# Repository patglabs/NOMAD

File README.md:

# NOMAD 
A laptop designed to be customisable, portable and open source

if you're in the hc slack make sure to join #pats-basement

## STATUS : ON HOLD DUE TO LACK OF FUNDS

## In brief:
Nomad is a laptop ive designed and am designing that features a lattepanda mu n100 at its center which handles all the compute. It uses a custom mainboard pcb that I designed to have 2 usb 3 type A ports exposed to the outside,
1 usb c 2.0 and 1 internal usb 2.0 which will go into an internal usb hub so that i can put an rtl sdr inside the laptop so i have an sdr everywhere i go. It uses a 14 inch hd display. A thinkpad keyboard. 3-4 5000mah lithium ion batteries in the standard
7mm thickness. Its passively cooled using an anodized aluminum sheet that will cover most of the bottom with the rest being 3d printed ideally in petg and assuming all goes to plan around it will be around 1.7cm thick. I estimate that it can acheive at least 6 hours of battery life with 4 5000mah battery while doing lite tasks. It also has m.2 slots. M key for nvme and e key for a wireless adapter.

## The vision:

A while ago i remember seeing a youtube short that really stuck with me, it was about a "hacker laptop and the short explained how it used a raspberry pi inside and had 18650 batteries and all and while it was a cool project i was blown away by the price, it costed over 1k usd and it was not very powerfull nor portable it felt like more of a cool gimmick than a tool. So I said one day I want to make something like that but ill make it the way i want. Itl have the things i want in a laptop: being compact and sturdy, easily fixable if something breaks, cheap, i can put custom stuff in it (like an rtl-sdr) and i wanted it to have decent battery life so that i can bring it anywhere and if i'm stuck somewhere with no power for 3 hours i can still work on stuff on it. Basically something that can be daily drivable when I dont have access to my desktop.

### pcb

Its pretty crowded, I recomend you open up the pcb in kicad you'll be able to zoom into stuff

(missing the 2 usb3 ports and the ddr4 so-dimm connector

note: pcb V2 is the latest pcb, but production wise they are the same its just a redraw of the schematic
so you want to look at the v2

### cad

### Bom

| Item | Price | Link |
|------|-------|------|
| Lattepanda MU + Lite Dev Carrier Board | 180 USD | [DFRobot](https://www.dfrobot.com/kit-004.html) |
| Display Controller | 22 USD | [AliExpress](https://www.aliexpress.com/item/1005008432586523.html?spm=a2g0o.productlist.main.12.6c4bwR7lwR7l8y&algo_pvid=8593971f-0f25-4dac-ac2b-4313578de187&algo_exp_id=8593971f-0f25-4dac-ac2b-4313578de187-11&pdp_ext_f=%7B%22order%22%3A%22-1%22%2C%22eval%22%3A%221%22%7D&pdp_npi=4%40dis%21CAD%2131.75%2126.99%21%21%21162.57%21138.20%21%402103247417527988213296838e3ecd%2112000045073927194%21sea%21CA%216086132031%21X&curPageLogUid=1h1893jWQeCE&utparam-url=scene%3Asearch%7Cquery_from%3A) |
| Display 14 inch | 42 USD | [AliExpress](https://www.aliexpress.com/item/1005003386237483.html?spm=a2g0o.productlist.main.20.787a5f1dEl49la&algo_pvid=1de636ed-d35d-4aee-a0d8-9a6b0865f511&algo_exp_id=1de636ed-d35d-4aee-a0d8-9a6b0865f511-19&pdp_ext_f=%7B%22order%22%3A%2223%22%2C%22eval%22%3A%221%22%7D&pdp_npi=4%40dis%21CAD%2168.99%2168.99%21%21%2149.21%2149.21%21%40210318ec17527987558765212ed2de%2112000025538273862%21sea%21CA%216086132031%21X&curPageLogUid=DP21csvKEzq9&utparam-url=scene%3Asearch%7Cquery_from%3A) |
| Reinforcement Sheet for Display | 4.50 USD | [AliExpress](https://www.aliexpress.com/item/1005005966208898.html?spm=a2g0o.productlist.main.4.46b44b90s4itPe&algo_pvid=2cadd10b-1e23-4d8a-baaa-58015ebbfa84&algo_exp_id=2cadd10b-1e23-4d8a-baaa-58015ebbfa84-3&pdp_ext_f=%7B%22order%22%3A%22911%22%2C%22eval%22%3A%221%22%7D&pdp_npi=4%40dis%21CAD%215.69%215.69%21%21%2129.16%2129.16%21%402103244417534139299131566ef5c8%2112000035086418949%21sea%21CA%216086132031%21X&curPageLogUid=P45FPnknGnQg&utparam-url=scene%3Asearch%7Cquery_from%3A) |
| SODIMM DDR4 Connector (C2979963) | - | [JLCPCB](https://jlcpcb.com/partdetail/FOXCONN-ASAA823_EARB07H/C2979963) |
| 5000 mAh Battery | 30 CAD × 3–4 | [Amazon](https://www.amazon.ca/5000mAh-755590-Lithium-Replacement-Electronic/dp/B0BG85CMFL/ref=sr_1_1_sspa?crid=1VN50572QX28K&dib=eyJ2IjoiMSJ9.UH2iT11CrxzaQwfjEOyYPhK1U5jypSDZNWR4AsOAj6AqUhiNM-AfuSVTdCHuEgDrhX1ioglR6OQ_EnFGpm1RMRGhI8XFnnH-OlCwdBPSY1DBLp_jPFmBZIQ1OtFXrNlPgc_Z7XODRqUUBo6_nUXE3vagri2b7yDxdF9CqiwkFz52h7MugKFeGZKHuOtqFd3e4pfhVFPoPNogyl6p7YN8Cja68egJHFHi3pZRJOaOmkVI7mTkMwltDyW_U-2lOJuCL-ofAm3b0rf8hjlGPR3D_fCmjXyqCv1V4x5C1jTn2eI.CyqpkaqJzNKz6gdU7nku_drLzpFhmbIbea_bnupkH2w&dib_tag=se&keywords=lithium+battery+5000mah&qid=1753592235&sprefix=lithium+battery+5000mah%2Caps%2C94&sr=8-1-spons&sp_csd=d2lkZ2V0TmFtZT1zcF9hdGY&psc=1) |
| Mainboard PCB | ~90 USD (estimate) | x |
| ThinkPad Keyboard | ~30–40 USD | - |

Note that I already have the thinkpad keyboard and the 3d printing filament but its pla so ill have to test petg in the future.

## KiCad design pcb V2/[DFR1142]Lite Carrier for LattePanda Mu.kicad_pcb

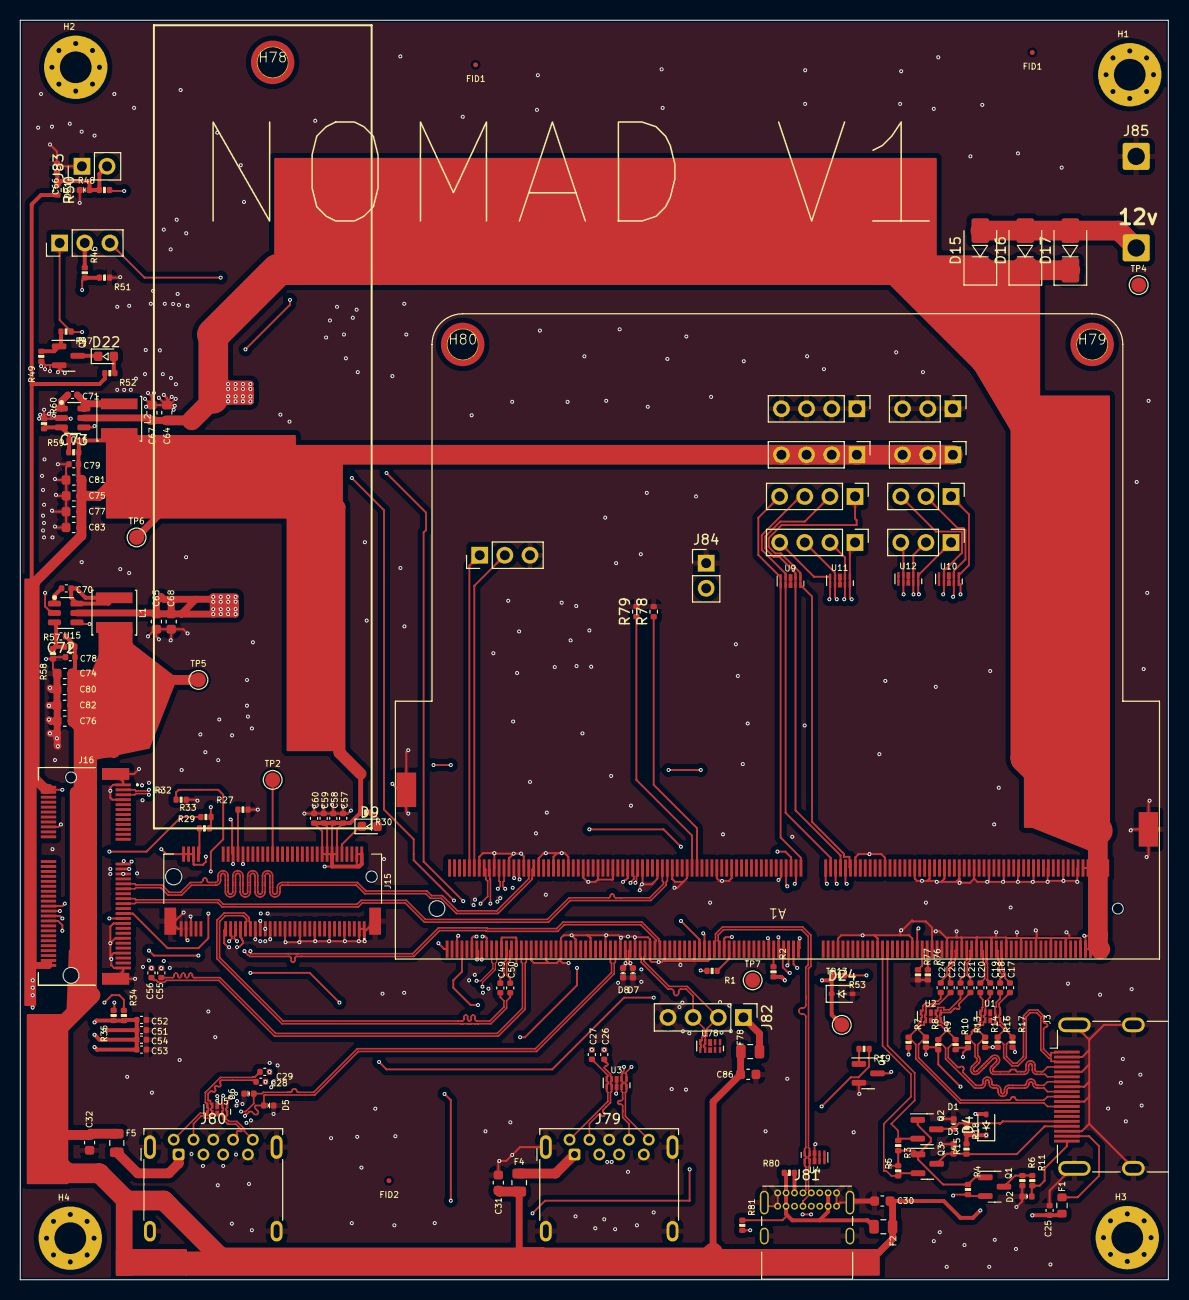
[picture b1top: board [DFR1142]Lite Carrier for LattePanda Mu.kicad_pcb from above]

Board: 4 copper layers, 116.0 x 127.2 mm, 168 parts (0 on the bottom side), 130 nets.

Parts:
A1: LattePanda_Mu; LattePanda_Module_H8.0mm_Horizontal
C17, C18, C19, C20, C21, C22, C23, C24, C25, C26, C27, C28, C29, C52, C54, C58, C60, C70, C71, C78, C79: 100nF/50V; C_0402_1005Metric
C30, C31, C32, C64, C65, C67, C68, C74, C75, C76, C77, C80, C81, C82, C83, C86: 22uF/10V; C_0603_1608Metric
C49, C50, C55, C56: 220nF/50V; C_0402_1005Metric
C51, C53, C57, C59: 10uF/10V; C_0402_1005Metric
C66: 1uF/16V; C_0402_1005Metric
C72, C73: 12pF/50V; C_0402_1005Metric
D1, D2, D3, D5, D6, D7, D8, D21: ESD5V0B03; D_0402_1005Metric
D4: 1N5819WS; D_SOD-323
D9, D22: LED_G; LED_0603_1608Metric
D15, D16, D17: SS54; D_SMA
D24: 3V3 Izt=5mA; D_SOD-323
F1: 6V/50mA; R_0603_1608Metric
F2, F78: 6V/1A; Fuse_0805_2012Metric
F4: 6V/2A; R_0805_2012Metric
F5: 6V/2A; Fuse_0805_2012Metric
FID1, FID1#2, FID2: Fiducial; Fiducial_0.5mm_Mask1mm
H1, H2, H3, H4: MountingHole_Pad; MountingHole_3.2mm_M3_Pad_Via
H78, H79, H80: MountingHole_Pad; MountingHole_3mm_M2_Pad_TopOnly
J1, J8, J10, J11, J14: Conn_01x03_Pin; PinHeader_1x03_P2.54mm_Vertical
J3: HDMI_A; HDMI_A_Molex_208658-1001_Horizontal
J7, J9, J12, J13, J82: Conn_01x04_Pin; PinHeader_1x04_P2.54mm_Vertical
J15: Bus_M.2_Socket_M; PCIe_M.2_Connectors_P=0.5mm_H=4.2mm_KeyM
J16: Bus_M.2_Socket_E; PCIe_M.2_Connectors_P=0.5mm_H=4.2mm_KeyE
J78, J85: Conn_01x01_Pin; SolderWire-1sqmm_1x01_D1.4mm_OD2.7mm
J79, J80: USB3_A; USB3_A_Molex_48393-001
J81: USB_C_Receptacle_USB2.0_16P; USB_C_Receptacle_GCT_USB4085
J83, J84: Conn_01x02_Pin; PinHeader_1x02_P2.54mm_Vertical
JP1: Jumper_3_Bridged12; PinHeader_1x03_P2.54mm_Vertical
L1, L2: 2.2uH/4.3A; L_Sunlord_SWPA4020S
Q1, Q8: 2N7002; SOT-23
Q2, Q3, Q4: 2SK3018; SOT-23
R1, R11, R47: 1K/1%; R_0402_1005Metric
R2, R34, R35, R49, R50, R58, R78, R79: 10K/1%; R_0402_1005Metric
R3, R5, R15, R18, R19, R30, R52, R53: 2.2K/1%; R_0402_1005Metric
R4: 1M/1%; R_0402_1005Metric
R6, R59: 21.5K/1%; R_0402_1005Metric
R7, R8, R9, R10, R13, R14, R16, R17: 470R/1%; R_0402_1005Metric
R27, R29, R32, R33: 0R/1%; R_0402_1005Metric
R46, R48: 100R/1%; R_0402_1005Metric
R51, R76, R77: 100K/1%; R_0402_1005Metric
R57: 75K/1%; R_0402_1005Metric
R60: 4.7K/1%; R_0402_1005Metric
R80, R81: 5.1K/1%; R_0402_1005Metric
TP2, TP4, TP5, TP6, TP7, TP13: TestPoint; TestPoint_Pad_D1.5mm
U1, U2: TPAZ1023-04F; Diodes_UDFN-10_1.0x2.5mm_P0.5mm
U3, U4, U5, U9, U10, U11, U12, U78: ULC0524P; Diodes_UDFN-10_1.0x2.5mm_P0.5mm
U15, U16: SY8253ADC; TSOT-23-6

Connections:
5V_HDMI_VCC: C25.1, D4.1 (K), F1.1, R15.1, R18.1
+3V3: C51.2, C52.2, C53.2, C54.2, C57.2, C58.2, C59.2, C60.2, C73.1, C75.2, C77.2, C79.1, C81.2, C83.2, J13.1, J13.2, J13.3, J13.4, J14.1, J14.2, J14.3, J15.2 (3.3V), J15.4 (3.3V), J15.12 (3.3V), J15.14 (3.3V), J15.16 (3.3V), J15.18 (3.3V), J15.70 (3.3V), J15.72 (3.3V), J15.74 (3.3V), J16.2 (3.3V), J16.4 (3.3V), J16.72 (3.3V), J16.74 (3.3V), L2.2, Q1.1 (G), Q2.1 (G), Q3.1 (G), R3.1, R4.1, R5.1, R30.2, R34.2, R35.1, R50.2, R52.2, R59.2, TP6.1
+5V: C30.2, C31.2, C32.2, C72.1, C74.2, C76.2, C78.1, C80.2, C82.2, C86.2, D4.2 (A), F2.1, F4.1, F5.1, F78.1, L1.2, R57.2, TP5.1
+12V: D15.2 (A), D16.2 (A), D17.2 (A), J78.1, TP4.1
+BATT: A1.115 (VBAT), R1.1
/GPIO/I2C2_SCL: A1.154 (I2C2_SCL), J9.1, U11.1, U11.10 (NC)
/GPIO/I2C2_SDA: A1.156 (I2C2_SDA), J7.1, U9.1, U9.10 (NC)
/GPIO/I2C3_SCL: A1.150 (I2C3_SCL), J9.2, U11.2, U11.9 (NC)
/GPIO/I2C3_SDA: A1.152 (I2C3_SDA), J7.2, U9.2, U9.9 (NC)
/GPIO/I2C4_SCL: A1.146 (I2C4_SCL), J9.3, U11.4, U11.7 (NC)
/GPIO/I2C4_SDA: A1.148 (I2C4_SDA), J7.3, U9.4, U9.7 (NC)
/GPIO/I2C5_SCL: A1.142 (I2C5_SCL), J9.4, U11.5, U11.6 (NC)
/GPIO/I2C5_SDA: A1.144 (I2C5_SDA), J7.4, U9.5, U9.6 (NC)
/GPIO/SOC_UART0_RX: A1.137 (UART0_RXD), J8.1, U10.1, U10.10 (NC)
/GPIO/SOC_UART0_TX: A1.139 (UART0_TXD), J10.1, U12.1, U12.10 (NC)
/GPIO/SOC_UART1_RX: A1.141 (UART1_RXD), J8.2, U10.2, U10.9 (NC)
/GPIO/SOC_UART1_TX: A1.143 (UART1_TXD), J10.2, U12.2, U12.9 (NC)
/GPIO/SOC_UART2_RX: A1.140 (UART2_RXD), J8.3, U10.4, U10.7 (NC)
/GPIO/SOC_UART2_TX: A1.138 (UART2_TXD), J10.3, U12.4, U12.7 (NC)
/HDMI/DDC_SCL: D1.2 (A2), J3.15 (SCL), Q2.3 (D), R15.2
/HDMI/DDC_SDA: D3.2 (A2), J3.16 (SDA), Q3.3 (D), R18.2
/HDMI/DDI_B_DDC_SCL: A1.171 (DDIB_DDC_SCL), Q2.2 (S), R5.2
/HDMI/DDI_B_DDC_SDA: A1.169 (DDIB_DDC_SDA), Q3.2 (S), R3.2
/HDMI/DDI_B_HPD: A1.183 (DDIB_HPD), Q1.2 (S), R4.2
/HDMI/DDI_B_TX0+: A1.217 (DDIB_TX0+), C17.1
/HDMI/DDI_B_TX0-: A1.215 (DDIB_TX0-), C18.1
/HDMI/DDI_B_TX1+: A1.211 (DDIB_TX1+), C19.1
/HDMI/DDI_B_TX1-: A1.209 (DDIB_TX1-), C20.1
/HDMI/DDI_B_TX2+: A1.205 (DDIB_TX2+), C21.1
/HDMI/DDI_B_TX2-: A1.203 (DDIB_TX2-), C22.1
/HDMI/DDI_B_TX3+: A1.199 (DDIB_TX3+), C23.1
/HDMI/DDI_B_TX3-: A1.197 (DDIB_TX3-), C24.1
/HDMI/HPD: D2.2 (A2), J3.19 (HPD), R11.2
/HDMI/TMDS_CK+: C23.2, J3.10 (CK+), R8.1, U2.4, U2.7 (NC)
/HDMI/TMDS_CK-: C24.2, J3.12 (CK-), R7.1, U2.5, U2.6 (NC)
/HDMI/TMDS_D0+: C21.2, J3.7 (D0+), R10.1, U2.1, U2.10 (NC)
/HDMI/TMDS_D0-: C22.2, J3.9 (D0-), R9.1, U2.2, U2.9 (NC)
/HDMI/TMDS_D1+: C19.2, J3.4 (D1+), R14.1, U1.4, U1.7 (NC)
/HDMI/TMDS_D1-: C20.2, J3.6 (D1-), R13.1, U1.5, U1.6 (NC)
/HDMI/TMDS_D2+: C17.2, J3.1 (D2+), R17.1, U1.1, U1.10 (NC)
/HDMI/TMDS_D2-: C18.2, J3.3 (D2-), R16.1, U1.2, U1.9 (NC)
/LattePanda Module/HSIO_0_TX+: A1.13 (HSIO0_TX+), C27.1
/LattePanda Module/HSIO_0_TX-: A1.15 (HSIO0_TX-), C26.1
/LattePanda Module/HSIO_1_TX+: A1.19 (HSIO1_TX+), C29.1
/LattePanda Module/HSIO_1_TX-: A1.21 (HSIO1_TX-), C28.1
/LattePanda Module/HSIO_2_RX+: A1.28 (HSIO2_RX+), J15.43 (PERp0/SATA-B-)
/LattePanda Module/HSIO_2_RX-: A1.30 (HSIO2_RX-), J15.41 (PERn0/SATA-B+)
/LattePanda Module/HSIO_2_TX+: A1.25 (HSIO2_TX+), C49.1
/LattePanda Module/HSIO_2_TX-: A1.27 (HSIO2_TX-), C50.1
/LattePanda Module/HSIO_3_RX+: A1.34 (HSIO3_RX+), J16.41 (PERp0)
/LattePanda Module/HSIO_3_RX-: A1.36 (HSIO3_RX-), J16.43 (PERn0)
/LattePanda Module/HSIO_3_TX+: A1.31 (HSIO3_TX+), C55.1
/LattePanda Module/HSIO_3_TX-: A1.33 (HSIO3_TX-), C56.1
/LattePanda Module/REFCLK0+: A1.85 (REFCLK0+), J15.53 (REFCLKn)
/LattePanda Module/REFCLK0-: A1.87 (REFCLK0-), J15.55 (REFCLKp)
/LattePanda Module/REFCLK3+: A1.88 (REFCLK3+), J16.47 (REFCLKp0)
/LattePanda Module/REFCLK3-: A1.90 (REFCLK3-), J16.49 (REFCLKn0)
/LattePanda Module/SLS_S3: A1.7 (SLS_S3), JP1.3 (B)
/LattePanda Module/SUSCLK_WIFI: A1.131 (SUSCLK), R29.2, R33.2
/LattePanda Module/USB_2_P7+: A1.76 (USB2_P7+), J16.3 (USB_D+)
/LattePanda Module/USB_2_P7-: A1.78 (USB2_P7-), J16.5 (USB_D-)
/LattePanda Module/~PWR_SW: A1.1 (~PWRBTN), R48.2
/M.2 E&M Key/CON_PCIE_TX_0+: C55.2, J16.35 (PETp0)
/M.2 E&M Key/CON_PCIE_TX_0-: C56.2, J16.37 (PETn0)
/M.2 E&M Key/CON_PCIE_TX_1+: C49.2, J15.49 (PETp0/SATA-A+)
/M.2 E&M Key/CON_PCIE_TX_1-: C50.2, J15.47 (PETn0/SATA-A-)
/M.2 E&M Key/~CLKREQE: J16.53 (~CLKREQ0), R32.1
/M.2 E&M Key/~CLKREQM: J15.52 (~CLKREQ), R27.1
/PSU/PWR_EN: R46.2, R51.2, U15.4 (EN), U16.4 (EN)
/USB2.0&USB3.0/CON_USB1_D_N: A1.109 (USB2_P5-), J81.A7 (D-), J81.B7 (D-), U4.2, U4.9 (NC)
/USB2.0&USB3.0/CON_USB1_D_P: A1.111 (USB2_P5+), J81.A6 (D+), J81.B6 (D+), U4.1, U4.10 (NC)
/USB2.0&USB3.0/CON_USB2_D_N: A1.79 (USB2_P3-), J82.3, U78.5, U78.6 (NC)
/USB2.0&USB3.0/CON_USB2_D_P: A1.81 (USB2_P3+), J82.2, U78.4, U78.7 (NC)
/USB2.0&USB3.0/CON_USB3_D_N: A1.73 (USB2_P2-), D8.2 (A2), J79.2 (D-)
/USB2.0&USB3.0/CON_USB3_D_P: A1.75 (USB2_P2+), D7.2 (A2), J79.3 (D+)
/USB2.0&USB3.0/CON_USB3_SSRX_N: A1.18 (HSIO0_RX-), J79.5 (SSRX-), U3.1, U3.10 (NC)
/USB2.0&USB3.0/CON_USB3_SSRX_P: A1.16 (HSIO0_RX+), J79.6 (SSRX+), U3.2, U3.9 (NC)
/USB2.0&USB3.0/CON_USB3_SSTX_N: C26.2, J79.8 (SSTX-), U3.4, U3.7 (NC)
/USB2.0&USB3.0/CON_USB3_SSTX_P: C27.2, J79.9 (SSTX+), U3.5, U3.6 (NC)
/USB2.0&USB3.0/CON_USB4_D_N: A1.67 (USB2_P1-), D6.2 (A2), J80.2 (D-)
/USB2.0&USB3.0/CON_USB4_D_P: A1.69 (USB2_P1+), D5.2 (A2), J80.3 (D+)
/USB2.0&USB3.0/CON_USB4_SSRX_N: A1.24 (HSIO1_RX-), J80.5 (SSRX-), U5.1, U5.10 (NC)
/USB2.0&USB3.0/CON_USB4_SSRX_P: A1.22 (HSIO1_RX+), J80.6 (SSRX+), U5.2, U5.9 (NC)
/USB2.0&USB3.0/CON_USB4_SSTX_N: C28.2, J80.8 (SSTX-), U5.4, U5.7 (NC)
/USB2.0&USB3.0/CON_USB4_SSTX_P: C29.2, J80.9 (SSTX+), U5.5, U5.6 (NC)
/~PLT_RST: A1.105 (~PLTRST), J15.50 (~PERST), J16.52 (~PERST0)
/~PWR_LED/~PSON: A1.5 (SLS_S0), JP1.1 (A), R19.1, R47.1
/~WAKE: A1.103 (~WAKE), J15.54 (~PEWAKE), J16.55 (~PEWAKE0)
GND: A1.11 (GND), A1.14 (GND), A1.17 (GND), A1.20 (GND), A1.23 (GND), A1.26 (GND), A1.29 (GND), A1.32 (GND), A1.35 (GND), A1.38 (GND), A1.41 (GND), A1.44 (GND), A1.47 (GND), A1.50 (GND), A1.53 (GND), A1.56 (GND), A1.59 (GND), A1.62 (GND), A1.65 (GND), A1.68 (GND), A1.71 (GND), A1.74 (GND), A1.77 (GND), A1.80 (GND), A1.83 (GND), A1.86 (GND), A1.89 (GND), A1.92 (GND), A1.95 (GND), A1.98 (GND), A1.101 (GND), A1.107 (GND), A1.110 (GND), A1.113 (GND), A1.116 (GND), A1.135 (GND), A1.136 (GND), A1.151 (GND), A1.158 (GND), A1.167 (GND), A1.170 (GND), A1.181 (GND), A1.182 (GND), A1.188 (GND), A1.189 (GND), A1.194 (GND), A1.195 (GND), A1.200 (GND), A1.201 (GND), A1.206 (GND), A1.207 (GND), A1.212 (GND), A1.213 (GND), A1.218 (GND), A1.219 (GND), A1.224 (GND), A1.225 (GND), A1.230 (GND), A1.231 (GND), A1.236 (GND), A1.237 (GND), A1.242 (GND), A1.243 (GND), A1.248 (GND), A1.249 (GND), A1.MP (Mountinge_Pads), C25.2, C30.1, C31.1, C32.1, C51.1, C52.1, C53.1, C54.1, C57.1, C58.1, C59.1, C60.1, C64.1, C65.1, C66.2, C67.1, C68.1, C74.1, C75.1, C76.1, C77.1, C78.2, C79.2, C80.1, C81.1, C82.1, C83.1, C86.1, D1.1 (A1), D2.1 (A1), D3.1 (A1), D5.1 (A1), D6.1 (A1), D7.1 (A1), D8.1 (A1), D21.1 (A1), D24.2 (A), J1.3, J3.2 (D2S), J3.5 (D1S), J3.8 (D0S), J3.11 (CKS), J3.17 (GND), J3.SH, J11.1, J11.2, J11.3, J12.1, J12.2, J12.3, J12.4, J15.1 (GND), J15.3 (GND), J15.9 (GND), J15.15 (GND), J15.21 (GND), J15.27 (GND), J15.33 (GND), J15.39 (GND), J15.45 (GND), J15.51 (GND), J15.57 (GND), J15.71 (GND), J15.73 (GND), J15.75 (GND), J15.MP1, J15.MP2, J16.1 (GND), J16.7 (GND), J16.18 (GND), J16.33 (GND), J16.39 (GND), J16.45 (GND), J16.51 (GND), J16.57 (GND), J16.63 (GND), J16.69 (GND), J16.75 (GND), J16.MP1, J16.MP2, J79.4 (GND), J79.7 (DRAIN), J79.10 (SHIELD), J80.4 (GND), J80.7 (DRAIN), J80.10 (SHIELD), J81.A1 (GND), J81.A12 (GND), J81.B1 (GND), J81.B12 (GND), J81.S1 (SHIELD), J82.4, J83.1, J84.1, J85.1, Q4.2 (S), Q8.2 (S), R6.2, R27.2, R32.2, R49.1, R51.1, R58.1, R60.1, R76.2, R77.2, R78.2, R79.2, U1.3 (VSS), U1.8 (VSS), U2.3 (VSS), U2.8 (VSS), U3.3 (VSS), U3.8 (VSS), U4.3 (VSS), U4.8 (VSS), U5.3 (VSS), U5.8 (VSS), U9.3 (VSS), U9.8 (VSS), U10.3 (VSS), U10.8 (VSS), U11.3 (VSS), U11.8 (VSS), U12.3 (VSS), U12.8 (VSS), U15.2 (GND), U16.2 (GND)
unnamed: A1.12 (SIO_UART_RX), J1.2
unnamed: A1.10 (SIO_UART_TX), J1.1
unnamed: A1.187 (TCP0_HPD), R76.1
unnamed: A1.185 (TCP1_HPD), R77.1
unnamed: A1.133 (~BIOS_SEL), R2.1, TP7.1
unnamed: A1.100 (~CLKREQ3), R79.1
unnamed: A1.102 (~CLKREQ4), R78.1
unnamed: D9.2 (A), R30.1
unnamed: D9.1 (K), J15.10 (DAS/~DSS/~LED1)
unnamed: C66.1, D21.2 (A2), J83.2, R48.1, R50.1
unnamed: D22.2 (A), R52.1
unnamed: D22.1 (K), Q8.3 (D)
unnamed: F2.2, J81.A4 (VBUS), J81.A9 (VBUS), J81.B4 (VBUS), J81.B9 (VBUS), R80.1, R81.1
unnamed: F1.2, J3.18 (+5V)
unnamed: J15.38 (DEVSLP), TP2.1
unnamed: J15.68 (SUSCLK), R29.1
unnamed: J16.50 (SUSCLK), R33.1
unnamed: J16.56 (~W_DISABLE1), R34.1
unnamed: J16.54 (~W_DISABLE2), R35.2
unnamed: F4.2, J79.1 (VBUS)
unnamed: F5.2, J80.1 (VBUS)
unnamed: J81.A5 (CC1), R80.2
unnamed: J81.B5 (CC2), R81.2
unnamed: F78.2, J82.1
unnamed: J84.2, R1.2
unnamed: JP1.2 (C), R46.1
unnamed: Q1.3 (D), R6.1, R11.1
unnamed: Q4.3 (D), R7.2, R8.2, R9.2, R10.2, R13.2, R14.2, R16.2, R17.2
unnamed: Q4.1 (G), R19.2
unnamed: Q8.1 (G), R47.2, R49.2
unnamed: U10.5, U10.6 (NC)
unnamed: U12.5, U12.6 (NC)
unnamed: C70.2, U15.1 (BOOST)
unnamed: C72.2, R57.1, R58.2, U15.3 (FB)
unnamed: C70.1, L1.1, U15.6 (SW)
unnamed: C71.2, U16.1 (BOOST)
unnamed: C73.2, R59.1, R60.2, U16.3 (FB)
unnamed: C71.1, L2.1, U16.6 (SW)
unnamed: U78.3 (VSS), U78.8 (VSS)
VDC: A1.250 (VIN), A1.251 (VIN), A1.252 (VIN), A1.253 (VIN), A1.254 (VIN), A1.255 (VIN), A1.256 (VIN), A1.257 (VIN), A1.258 (VIN), A1.259 (VIN), A1.260 (VIN), C64.2, C65.2, C67.2, C68.2, D15.1 (K), D16.1 (K), D17.1 (K), R53.1, U15.5 (VIN), U16.5 (VIN)
VPullup: D24.1 (K), R2.2, R53.2, TP13.1

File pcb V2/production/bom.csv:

Designator,Footprint,Quantity,Value,LCSC Part #
A1,LattePanda_Module_H8.0mm_Horizontal,1,LattePanda_Mu,
"C17, C18, C19, C20, C21, C22, C23, C24, C25, C26, C27, C28, C29, C52, C54, C58, C60, C70, C71, C78, C79",0402,21,100nF/50V,
"C30, C31, C32, C64, C65, C67, C68, C74, C75, C76, C77, C80, C81, C82, C83, C86",0603,16,22uF/10V,
"C49, C50, C55, C56",0402,4,220nF/50V,
"C51, C53, C57, C59",0402,4,10uF/10V,
C66,0402,1,1uF/16V,
"D1, D2, D21, D3, D5, D6, D7, D8",0402,8,ESD5V0B03,
"D15, D16, D17",D_SMA,3,SS54,
"D22, D9",0603,2,LED_G,
D24,D_SOD-323,1,3V3 Izt=5mA,
D4,D_SOD-323,1,1N5819WS,
F1,0603,1,6V/50mA,
"F2, F78",0805,2,6V/1A,
"F4, F5",0805,2,6V/2A,
"J1, J10, J11, J14, J8",PinHeader_1x03_P2.54mm_Vertical,5,Conn_01x03_Pin,
"J12, J13, J7, J82, J9",PinHeader_1x04_P2.54mm_Vertical,5,Conn_01x04_Pin,
J15,PCIe_M.2_Connectors_P=0.5mm_H=4.2mm_KeyM,1,Bus_M.2_Socket_M,
J16,PCIe_M.2_Connectors_P=0.5mm_H=4.2mm_KeyE,1,Bus_M.2_Socket_E,
J3,HDMI_A_Molex_208658-1001_Horizontal,1,HDMI_A,
"J78, J85",SolderWire-1sqmm_1x01_D1.4mm_OD2.7mm,2,Conn_01x01_Pin,
"J79, J80",USB3_A_Molex_48393-001,2,USB3_A,
J81,USB_C_Receptacle_GCT_USB4085,1,USB_C_Receptacle_USB2.0_16P,
"J83, J84",PinHeader_1x02_P2.54mm_Vertical,2,Conn_01x02_Pin,
JP1,PinHeader_1x03_P2.54mm_Vertical,1,Jumper_3_Bridged12,
"L1, L2",L_Sunlord_SWPA4020S,2,2.2uH/4.3A,
"Q1, Q8",SOT-23,2,2N7002,
"Q2, Q3, Q4",SOT-23,3,2SK3018,
"R1, R11, R47",0402,3,1K/1%,
"R10, R13, R14, R16, R17, R7, R8, R9",0402,8,470R/1%,
"R15, R18, R19, R3, R30, R5, R52, R53",0402,8,2.2K/1%,
"R2, R34, R35, R49, R58, R78, R79",0402,7,10K/1%,
"R27, R29, R32, R33",0402,4,0R/1%,
R4,0402,1,1M/1%,
"R46, R48",0402,2,100R/1%,
"R51, R76, R77",0402,3,100K/1%,
R57,0402,1,75K/1%,
"R59, R6",0402,2,21.5K/1%,
R60,0402,1,4.7K/1%,
"R80, R81",0402,2,5.1K/1%,
TP2,TestPoint_Pad_D1.5mm,1,TestPoint,
"U1, U2",Diodes_UDFN-10_1.0x2.5mm_P0.5mm,2,TPAZ1023-04F,
"U10, U11, U12, U3, U4, U5, U78, U9",Diodes_UDFN-10_1.0x2.5mm_P0.5mm,8,ULC0524P,
"U15, U16",TSOT-23-6,2,SY8253ADC,

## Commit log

2025-07-20 a lot more routing has been done now
2025-07-21 components all now placed
2025-07-21 routing almost completely done if not done exept gnd
2025-07-21 before loading 12v in change
2025-07-21 before i aply ungrounding changes to moutning holes
2025-07-22 looking good i think done exept 23d models
2025-07-23 pcb is ready for production
2025-07-23 gerbers are ready all done
2025-08-11 aug 11
2025-08-12 done redrawing schematic
2025-08-12 updated cad
2026-05-18 Update README with project status and details
    Added status update and improved project description.
